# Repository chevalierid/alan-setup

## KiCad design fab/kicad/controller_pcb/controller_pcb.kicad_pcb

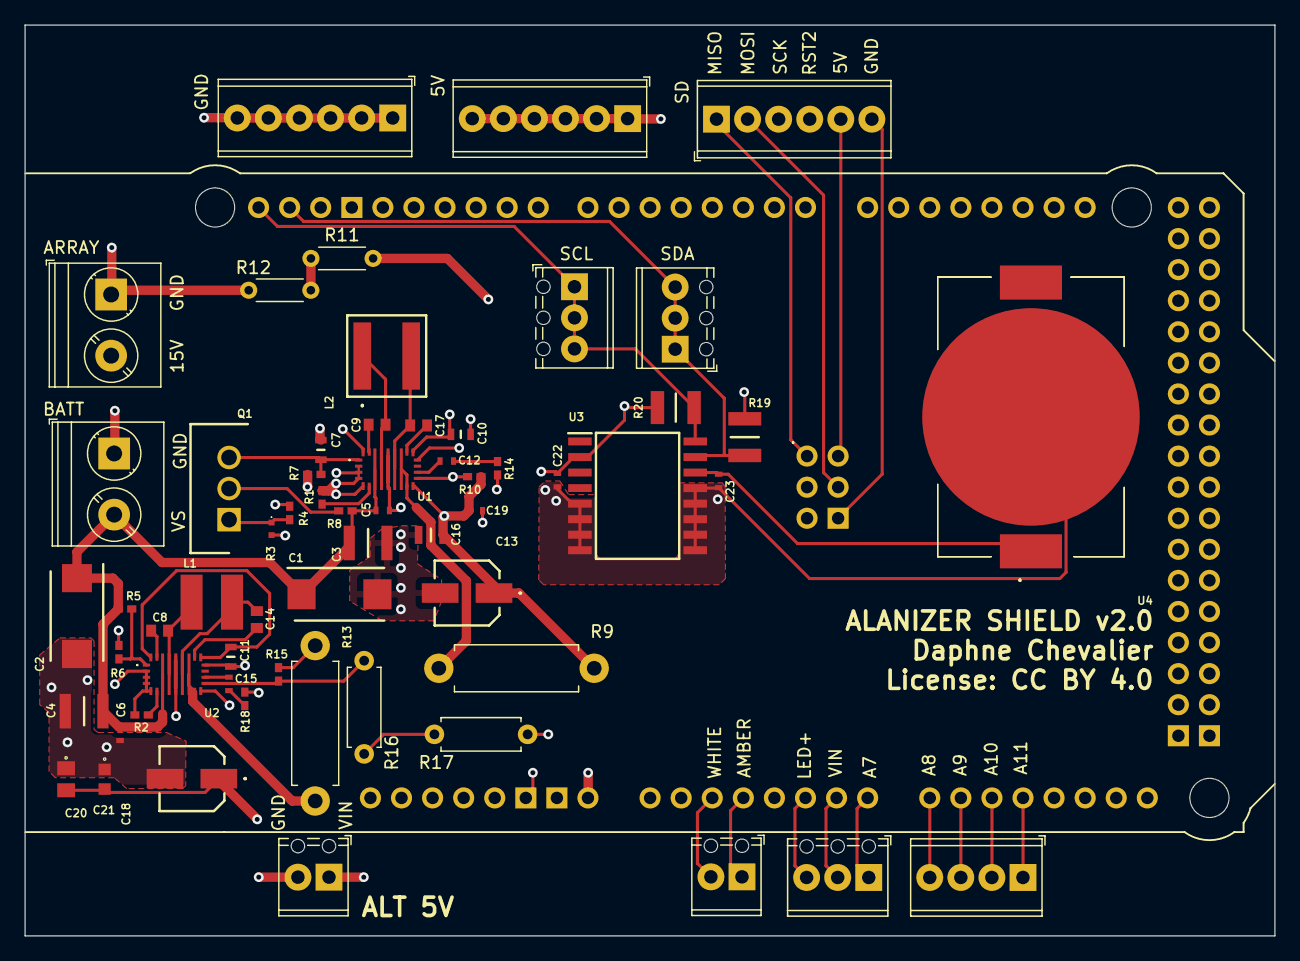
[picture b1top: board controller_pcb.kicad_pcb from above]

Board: 4 copper layers, 102.2 x 74.4 mm, 62 parts (0 on the bottom side), 49 nets.

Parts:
A1: Arduino_Mega2560_R3_Shield; mega_modified
C1, C2: EEFCX1E330R; CAPPM7343X200N
C3, C4: C3225X7R1H106M250AC; CAPC3225X230N
C5, C6, C19: C1005X5R1V105K050BC; CAPC1005X55N
C7, C10, C11: C1608X6S1C475K080AC; CAPC1608X80N
C8, C9, C14, C17: EMK107B7104KA-T; CAPC1608X95N
C12, C22, C23: GRM155R70J104KA01D; CAPC1005X55N
C13: 25SVPF27MX; 16SVF82M
C15: GRM155R70J473KA01D; CAPC1005X55N
C16: C2012X5R1V156M125AC; CAPC2012X145N
C18: 10SVPC68MV; 16SVF82M
C20: C0805C106K8PACTU; C0805
C21: C0603C105Z8VACTU; C0603
J1: Screw_Terminal_01x04; TerminalBlock_Phoenix_MPT-0,5-4-2.54_1x04_P2.54mm_Horizontal
J2, J3, J4: Screw_Terminal_01x03; TerminalBlock_Phoenix_MPT-0,5-3-2.54_1x03_P2.54mm_Horizontal
J5, J6, J11: Screw_Terminal_01x06; TerminalBlock_Phoenix_MPT-0,5-6-2.54_1x06_P2.54mm_Horizontal
J7, J9: Screw_Terminal_01x02; TerminalBlock_Phoenix_MPT-0,5-2-2.54_1x02_P2.54mm_Horizontal
J8, J10: 1935161; TerminalBlock_Phoenix_PT-1,5-2-5.0-H_1x02_P5.00mm_Horizontal
L1: SDR0403-4R7ML; SDR0403
L2: 74439346100
Q1: IRLZ44N; TO254P469X1042X1967-3P
R1, R2: CRCW040248K7FKED; RESC1005X40N
R3: ERJ-2RKF2400X; ERJ2RKD1004X
R4: CRCW040210K0FKED; RESC1005X40N
R5, R8: CRCW0402301KFKED; RESC1005X40N
R6, R7, R10, R15: CRCW0402100KFKED; RESC1005X40N
R9, R13: WLBR050FET; R_Axial_DIN0411_L9.9mm_D3.6mm_P12.70mm_Horizontal
R11: CFM14JT8K20; R_Axial_DIN0204_L3.6mm_D1.6mm_P5.08mm_Horizontal
R12: MBA02040C7320FRP00; R_Axial_DIN0204_L3.6mm_D1.6mm_P5.08mm_Horizontal
R14: CRCW0402301RFKED; RESC1005X40N
R16: RN55D3202FB14; R_Axial_DIN0207_L6.3mm_D2.5mm_P7.62mm_Horizontal
R17: CF14JT620R; R_Axial_DIN0207_L6.3mm_D2.5mm_P7.62mm_Horizontal
R18: CRCW040213K0FKED; RESC1005X40N
R19, R20: CRCW12104K70JNEA; RESC3225X60N
U1, U2: TPS55289RYQR; TPS552892QWRYQRQ1
U3: DS3231SN; SOIC127P1032X265-16N
U4: BK-912-TR; BK912TR

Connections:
A4: A1.A4, R3.2
BATT+: C1.1 (K), C2.1 (K), C3.2, C4.2, C5.2, C6.2, J10.2, R5.2, R8.2, U1.7 (VIN), U2.7 (VIN)
BOOT1: C9.1, U1.20 (BOOT1)
BOOT1-2: C8.1, U2.20 (BOOT1)
BOOT2: C17.1, U1.19 (BOOT2)
BOOT2-2: C14.1, U2.19 (BOOT2)
GND: A1.GND2 (GND), C1.2, C2.2, C3.1, C4.1, C5.1, C6.1, C7.1, C10.1, C11.1, C13.2 (-), C16.1, C18.2 (-), C19.1, C20.1, C21.1, C22.1, C23.1, J5.1, J5.2, J5.3, J5.4, J5.5, J5.6, J7.2, J8.1, J10.1, R1.1, R2.1, R4.1, R6.1, R7.1, R12.1, R14.1, R17.1, R18.1, U1.2 (MODE), U1.3 (SCL), U1.4 (SDA), U1.5 (DITH/SYNC), U1.9 (PGND_1), U1.17 (AGND), U1.22 (PGND_2), U1.23 (PGND_3), U2.2 (MODE), U2.3 (SCL), U2.4 (SDA), U2.5 (DITH/SYNC), U2.9 (PGND_1), U2.17 (AGND), U2.22 (PGND_2), U2.23 (PGND_3), U3.5 (N.C._1), U3.6 (N.C._2), U3.7 (N.C._3), U3.8 (N.C._4), U3.9 (N.C._5), U3.10 (N.C._6), U3.11 (N.C._7), U3.12 (N.C._8), U3.13 (GND), U4.3 (-)
unnamed: A1.5V2 (SPI_5V), J11.5
unnamed: A1.A2, J9.2
unnamed: A1.A3, J9.1
unnamed: A1.A5, J2.3
unnamed: A1.A6, J2.2
unnamed: A1.A7, J2.1
unnamed: A1.A8, J1.4
unnamed: A1.A9, J1.3
unnamed: A1.A10, J1.2
unnamed: A1.A11, J1.1
unnamed: A1.GND4 (SPI_GND), J11.6
unnamed: A1.MISO (SPI_MISO), J11.1
unnamed: A1.MOSI (SPI_MOSI), J11.2
unnamed: A1.RST2 (SPI_RESET), J11.4
unnamed: A1.SCK (SPI_SCK), J11.3
unnamed: C7.2, Q1.3 (S), R7.2, U1.1 (EN/UVLO)
unnamed: C10.2, U1.18 (VCC), U1.21 (EXTVCC)
unnamed: C11.2, U2.18 (VCC), U2.21 (EXTVCC)
unnamed: C12.1, R14.2
unnamed: C12.2, U1.15 (COMP)
unnamed: C15.1, R18.2
unnamed: C15.2, U2.15 (COMP)
unnamed: C23.2, U3.14 (VBAT), U4.1 (+_1)
unnamed: Q1.1 (G), R3.1, R4.2
unnamed: Q1.2 (D), R8.1
unnamed: R1.2, U1.6 (FSW)
unnamed: R2.2, U2.6 (FSW)
unnamed: R5.1, R6.2, U2.1 (EN/UVLO)
unnamed: R9.2, U1.11 (VOUT), U1.12 (ISP)
unnamed: R10.1, R11.2, U1.14 (FB/~INT)
unnamed: R11.1, R12.2
unnamed: R13.2, U2.11 (VOUT), U2.12 (ISP)
unnamed: R15.1, R16.2, U2.14 (FB/~INT)
unnamed: R16.1, R17.2
SCL: A1.SCL, J3.1, J3.2, J3.3, R20.1, U3.16 (SCL)
SDA: A1.SDA, J4.1, J4.2, J4.3, R19.1, U3.15 (SDA)
SW1: C9.2, L2.1, U1.8 (SW1)
SW1-2: C8.2, L1.1, U2.8 (SW1)
SW2: C17.2, L2.2, U1.10 (SW2)
SW2-2: C14.2, L1.2, U2.10 (SW2)
V5+: A1.VIN, C18.1 (+), C20.2, C21.2, C22.2, J6.1, J6.2, J6.3, J6.4, J6.5, J6.6, J7.1, R13.1, R15.2, R19.2, R20.2, U2.13 (ISN), U3.2 (VCC)
V15+: C13.1 (+), C16.2, C19.2, J8.2, R9.1, R10.2, U1.13 (ISN)

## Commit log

2022-07-26 Add files via upload
    added scheduling code for turning light on and off
2022-08-04 Add files via upload
    Combined scheduling and sampling code
2022-08-19 Add files via upload
    Script and sketch to set epoch time on RTC using PySerial
2022-10-24 added alarm tester and sd tester v1
2022-10-24 updates to sd tester
2022-11-03 adding file to just test the light and write dummy sensor data
2022-11-03 switches light on and off every 5 seconds
2022-11-04 switches light on and off every hour while writing sensor data to file that changes name hourly (I think)
2022-11-04 fixed filename bug and switching bug; now switches every min for 10min
2023-05-09 override button functionality, improved printing including white and amber (printing to file commented out but functional)
2023-05-16 new script for testing all light settings and override feature
2023-05-16 changes ported over from the test_override file
2023-05-16 removed 500ms delay, releasing override always turns off light even when it shouldn't
2023-05-16 fixed override issue
2023-05-18 updated scheduling.r to eliminate use of deprecated package maptools
2023-05-31 added functioning site label generation script which also randomises the site treatments
2023-06-06 Portable lightmeter v1
2023-06-07 adding label generator and site allocation scripts
2023-06-07 adding sticky pi label generator script
2023-06-07 functioning audiomoth site allocator giving 1 2 3 8 9 12
2023-06-08 changed 5 day interval to 10 day interval
2023-07-01 programmed all the sites with this
2023-07-01 testing override function
2023-07-01 scheduling file now goes from current day rather than tomorrow
2023-07-12 concatenate and plot light sensing files
2023-07-13 function to plot data in range from site
2023-07-13 fixed filefinding & handling empty csvs
    also new "l" option for just plotting up to 250 counts (typical range for when light is on)
2024-02-01 reorganising and adding controller PCB files
2024-02-06 updated 15v and 5v schematics to support parallel design (both receiving 6V-20V battery input) and constant current via 1A current limit on the 15v regulator
2024-02-07 added RTC circuit just need to sub in battery clip when found. decided to keep current SD setup rather than integrating into PCB
2024-02-09 added MOSFET to 15V and finished connections (hopefully); next step annotation
2024-02-21 started layout; about to rename pins
2024-02-21 pins renamed, replaced some big caps, draft layout done for vregs
2024-02-22 draft board layout
2024-02-23 before renaming/merging ground nets
2024-03-28 final v1 PCB schematics
2024-03-28 remove nested repository reference
2024-03-28 import controller_pcb content
2024-04-04 a bunch of preprocessing in new rmd file
2024-04-12 almost finding changepoints and assigning interval to each observation
2024-04-12 finds intervals and puts them in a column
2024-04-15 fixing the changepoints code
2024-04-15 changepoints code needs some cleanup but should choose closest date from list now
2024-04-15 changepoints/intervals code works and status column works
2024-04-19 v2 of PCB
2024-04-29 old processing file and new refactored setup
2024-04-29 working biomass and count cleaning & box/whisker with geom_jitter and wilcoxon rank sum tests
2024-04-29 renamed the count script from pitfall_names to count
2024-07-01 before it's changed to fully switch labelledsites to sites
2024-07-03 scratch work in treatment-fixing area for manual changepoints preserved
2024-11-10 Add files via upload
    markdown all-in-one with biomass, size, count, and taxonomic count models

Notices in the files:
fab/kicad/controller_pcb/controller_pcb.kicad_pcb:
creativecommons.org/licenses/by/4.0
License: CC BY 4.0
